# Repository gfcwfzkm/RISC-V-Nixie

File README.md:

# RISC-V-Nixie
Nixie Clock using the GD32VF103 RISC-V microcontroller by GigaDevices and the swiss precise RTC RV-3032-C7 by Micro Crystal AG.

For tubes, IN-8 tubes will be used as they can be mounted into sockets. Since the original, soviet sockets are quite bulky, individual pin sockets will be mounted instead.

## Status
The current status of the project, which steps are done or still need to be do. Currently only revision A is in testing, a revision that has some slight imperfections that will be tackled in the next revision. Since parts have been already delivered, revision A will be used to extensively test the PCB, in particular the dimming of the tubes and the high-voltage step-up circuitery.
Task | Comments
------------ | -------------
Initial Schematic | :heavy_check_mark:
Initial Layout & BOM | :heavy_check_mark:
Assembling PCB | :heavy_check_mark:
Power-ON Test, Voltage levels | :heavy_check_mark:
Initialising / Testing the MCU | :heavy_check_mark:
Writing basic I/O functions | In Progress... :grey_question:
Writing the clock programm | -

## Images

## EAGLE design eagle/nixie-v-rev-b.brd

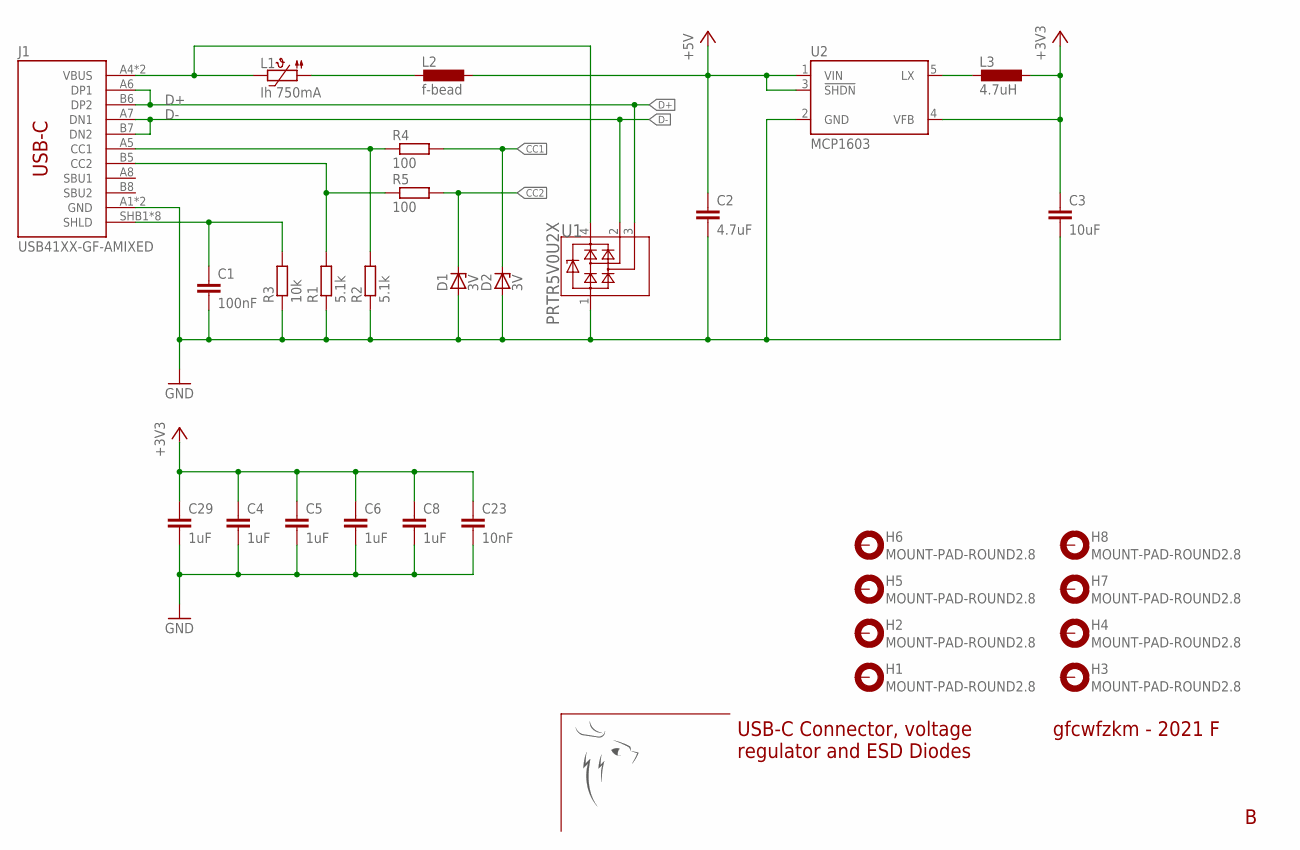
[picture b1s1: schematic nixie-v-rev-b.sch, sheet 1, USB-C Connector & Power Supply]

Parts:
C1: 100nF; C0603
C2: 4.7uF; C0805
C3: 10uF; C0805
C4, C5, C6, C8, C29: 1uF; C0603
C23: 10nF; C0603
D1, D2: 3V; SOD-523
H1, H2, H3, H4, H5, H6, H7, H8: MOUNT-PAD-ROUND2.8; 2,8-PAD
J1: USB41XX-GF-AMIXED; USB4105-GF-A
L1: Ih 750mA; R0805
L2: f-bead; R0805
L3: 4.7uH; R1210
R1, R2: 5.1k; R0603
R3: 10k; R0603
R4, R5: 100; R0603
U1: PRTR5V0U2X; SOT143B
U2: MCP1603; TSOT23-5
U$1: LOGO_PASCAL_GESELL30MM; LOGO_30MM

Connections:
+3V3: C3.1, C4.1, C5.1, C6.1, C8.1, C23.1, C29.1, L3.1, U2.4 (VFB); also elsewhere on the board
+5V: C2.1, L2.1, U2.1 (VIN), U2.3 (!SHDN); also elsewhere on the board
CC1: D2.C, R4.2; also elsewhere on the board
CC2: D1.C, R5.2; also elsewhere on the board
D+: J1.A6 (DP1), J1.B6 (DP2), U1.3; also elsewhere on the board
D-: J1.A7 (DN1), J1.B7 (DN2), U1.2; also elsewhere on the board
GND: C1.2, C2.2, C3.2, C4.2, C5.2, C6.2, C8.2, C23.2, C29.2, D1.A, D2.A, J1.A1 (GND), J1.B1 (GND), R1.1, R2.1, R3.1, U1.1, U2.2 (GND); also elsewhere on the board
LX: L3.2, U2.5 (LX)
unnamed: C1.1, J1.SHB1 (SHLD), J1.SHB2 (SHLD), J1.SHB3 (SHLD), J1.SHB4 (SHLD), J1.SHT1 (SHLD), J1.SHT2 (SHLD), J1.SHT3 (SHLD), J1.SHT4 (SHLD), R3.2
unnamed: J1.B5 (CC2), R1.2, R5.1
unnamed: J1.A5 (CC1), R2.2, R4.1
unnamed: L1.1, L2.2
VBUS: J1.A4 (VBUS), J1.B4 (VBUS), L1.2, U1.4

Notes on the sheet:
gfcwfzkm - 2021 F
USB-C Connector, voltage regulator and ESD Diodes

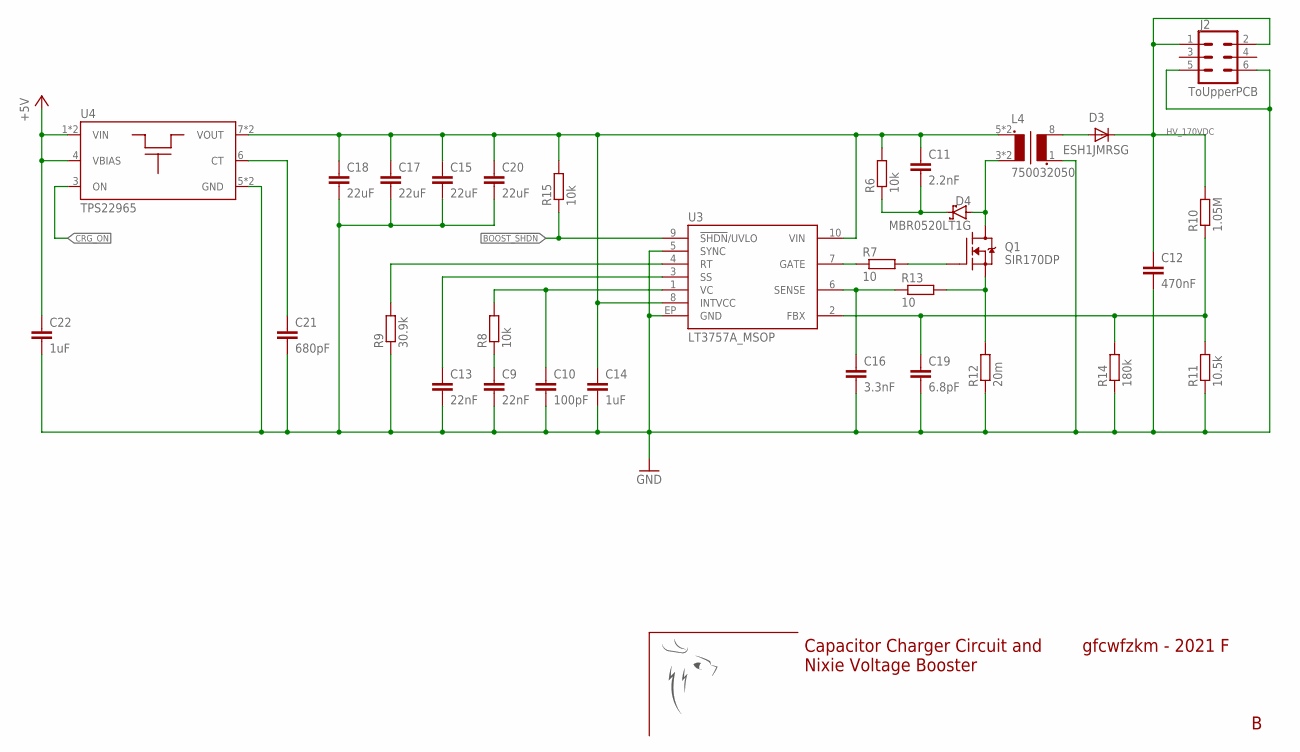
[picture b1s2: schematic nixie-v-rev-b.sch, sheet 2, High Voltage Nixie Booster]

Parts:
C9, C13: 22nF; C0603
C10: 100pF; C0603
C11: 2.2nF; C0603
C12: 470nF; C1812
C14, C22: 1uF; C0603
C15, C17, C18, C20: 22uF; C0805
C16: 3.3nF; C0603
C19: 6.8pF; C0603
C21: 680pF; C0603
D3: ESH1JMRSG; MICROSMA
D4: MBR0520LT1G; SOD-123
J2: ToUpperPCB; 2X3
L4: 750032050
Q1: SIR170DP; SO-08_POWERPAK
R6, R8, R15: 10k; R0603
R7, R13: 10; R0603
R9: 30.9k; R0603
R10: 1.05M; R0603
R11: 10.5k; R0603
R12: 20m; R0805
R14: 180k; R0603
U3: LT3757A_MSOP; MSOP10_POWER
U4: TPS22965; WSON-8
U$2: LOGO_PASCAL_GESELLEMPTY; EMPTY

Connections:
+5V: C22.1, U4.1 (VIN), U4.2 (VIN), U4.4 (VBIAS); also elsewhere on the board
BOOST_!SHDN: R15.1, U3.9 (!SHDN!/UVLO); also elsewhere on the board
CRG_ON: U4.3 (ON); also elsewhere on the board
FBX: C19.1, R10.1, R11.2, R14.2, U3.2 (FBX)
GATE: R7.1, U3.7 (GATE)
GND: C9.2, C10.2, C12.2, C13.2, C14.2, C15.2, C16.2, C17.2, C18.2, C19.2, C20.2, C21.2, C22.2, J2.5, J2.6, L4.1 (S1), R9.1, R11.1, R12.1, R14.1, U3.5 (SYNC), U3.EP (GND), U4.5 (GND), U4.TP (GND); also elsewhere on the board
HV_170VDC: C12.1, D3.C, J2.1, J2.2, R10.2
unnamed: C11.2, D4.C, R6.1
unnamed: Q1.4 (G), R7.2
unnamed: D3.A, L4.8 (S2)
unnamed: C9.1, R8.1
unnamed: Q1.1 (S), Q1.2 (S), Q1.3 (S), R12.2, R13.2
unnamed: D4.A, L4.3 (P2), L4.4 (P2), Q1.5 (D), Q1.6 (D), Q1.7 (D), Q1.8 (D), Q1.THERMAL (D)
unnamed: C21.1, U4.6 (CT)
RT: R9.2, U3.4 (RT)
SENSE: C16.1, R13.1, U3.6 (SENSE)
SS: C13.1, U3.3 (SS)
SUP_BOOST: C11.1, C14.1, C15.1, C17.1, C18.1, C20.1, L4.5 (P1), L4.6 (P1), R6.2, R15.2, U3.8 (INTVCC), U3.10 (VIN), U4.7 (VOUT), U4.8 (VOUT)
VC: C10.1, R8.2, U3.1 (VC)

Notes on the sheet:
Capacitor Charger Circuit and Nixie Voltage Booster
gfcwfzkm - 2021 F

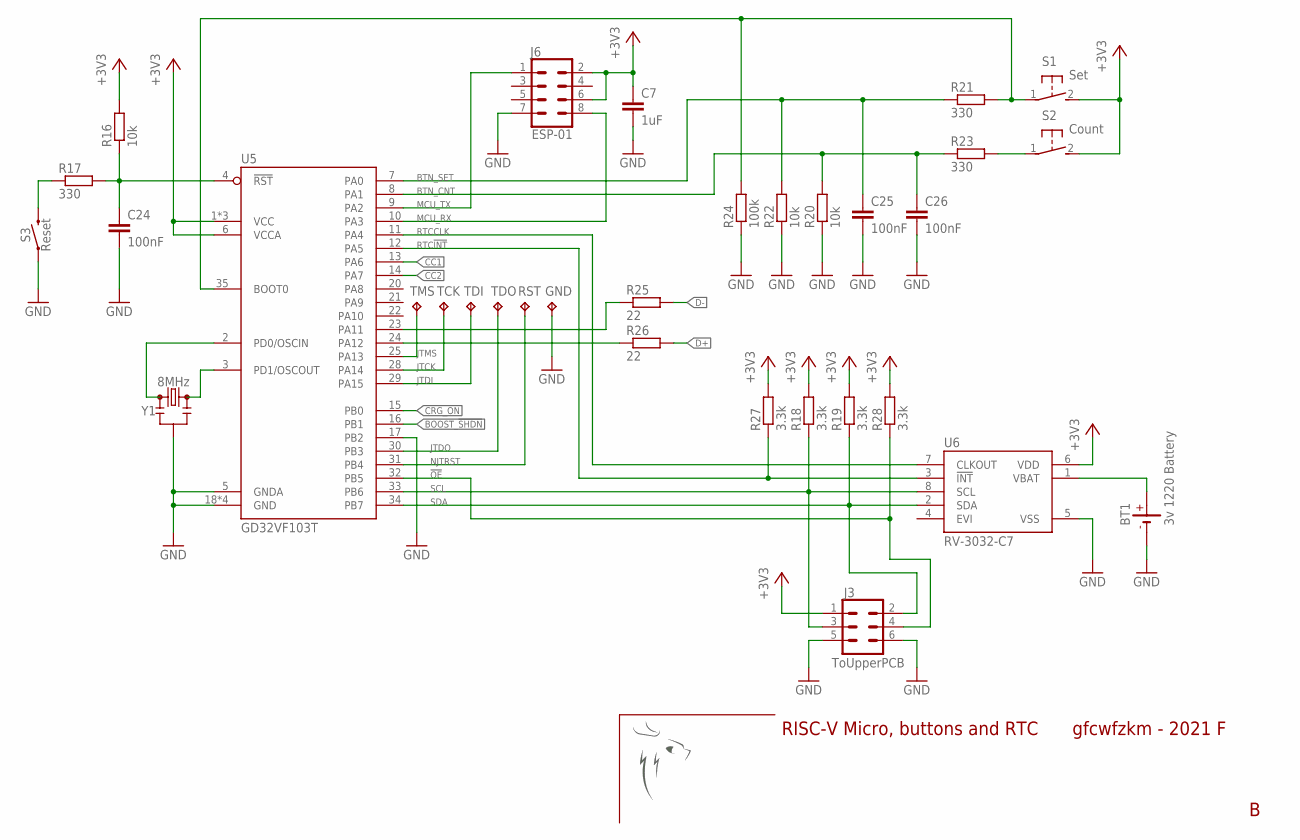
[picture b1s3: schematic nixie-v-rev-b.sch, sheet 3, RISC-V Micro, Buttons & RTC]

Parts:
BT1: 3v 1220 Battery; CH291-1220LF
C7: 1uF; C0603
C24, C25, C26: 100nF; C0603
GND: TPB1,27; B1,27
J3: ToUpperPCB; 2X3
J6: ESP-01; 2X4
R16, R20, R22: 10k; R0603
R17, R21, R23: 330; R0603
R18, R19, R27, R28: 3.3k; R0603
R24: 100k; R0603
R25, R26: 22; R0603
RST: TPB1,27; B1,27
S1: Set; B3F-31XX
S2: Count; B3F-31XX
S3: Reset; TACTILE_SWITCH_SMD_6.0X3.5MM
TCK: TPB1,27; B1,27
TDI: TPB1,27; B1,27
TDO: TPB1,27; B1,27
TMS: TPB1,27; B1,27
U5: GD32VF103T; QFN-36
U6: RV-3032-C7; RV-3028-C7
U$3: LOGO_PASCAL_GESELLEMPTY; EMPTY
Y1: 8MHz; RESONATOR-SMD-3.2X1.3

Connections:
!OE: J3.4, R28.1, U5.32 (PB5)
+3V3: C7.1, J3.1, J6.2, J6.6, R16.2, R18.2, R19.2, R27.2, R28.2, S1.2 (S), S2.2 (S), U5.1 (VCC), U5.6 (VCCA), U5.19 (VCC), U5.27 (VCC), U6.6 (VDD); also elsewhere on the board
BOOST_!SHDN: U5.16 (PB1); also elsewhere on the board
BTN_CNT: C26.1, R20.2, R23.1, U5.8 (PA1)
BTN_SET: C25.1, R21.1, R22.2, U5.7 (PA0)
CC1: U5.13 (PA6); also elsewhere on the board
CC2: U5.14 (PA7); also elsewhere on the board
CRG_ON: U5.15 (PB0); also elsewhere on the board
D+: R26.2; also elsewhere on the board
D-: R25.2; also elsewhere on the board
GND: BT1.-, C7.2, C24.2, C25.2, C26.2, GND.TP, J3.5, J3.6, J6.7, R20.1, R22.1, R24.1, S3.1, U5.5 (GNDA), U5.17 (PB2), U5.18 (GND), U5.26 (GND), U5.36 (GND), U5.EP (GND), U6.5 (VSS), Y1.2; also elsewhere on the board
JTCK: TCK.TP, U5.28 (PA14)
JTDI: TDI.TP, U5.29 (PA15)
JTDO: TDO.TP, U5.30 (PB3)
JTMS: TMS.TP, U5.25 (PA13)
MCU_RX: J6.8, U5.10 (PA3)
MCU_TX: J6.1, U5.9 (PA2)
unnamed: C24.1, R16.1, R17.2, U5.4 (!RST)
unnamed: R26.1, U5.24 (PA12)
unnamed: R23.2, S2.1
unnamed: U5.3 (PD1/OSCOUT), Y1.3
unnamed: R21.2, R24.2, S1.1, U5.35 (BOOT0)
unnamed: R17.1, S3.2
unnamed: U5.2 (PD0/OSCIN), Y1.1
unnamed: R25.1, U5.23 (PA11)
unnamed: BT1.+, U6.1 (VBAT)
NJTRST: RST.TP, U5.31 (PB4)
RTC!INT: R27.1, U5.12 (PA5), U6.3 (!INT)
RTCCLK: U5.11 (PA4), U6.7 (CLKOUT)
SCL: J3.3, R18.1, U5.33 (PB6), U6.8 (SCL)
SDA: J3.2, R19.1, U5.34 (PB7), U6.2 (SDA)

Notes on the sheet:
RISC-V Micro, buttons and RTC
gfcwfzkm - 2021 F

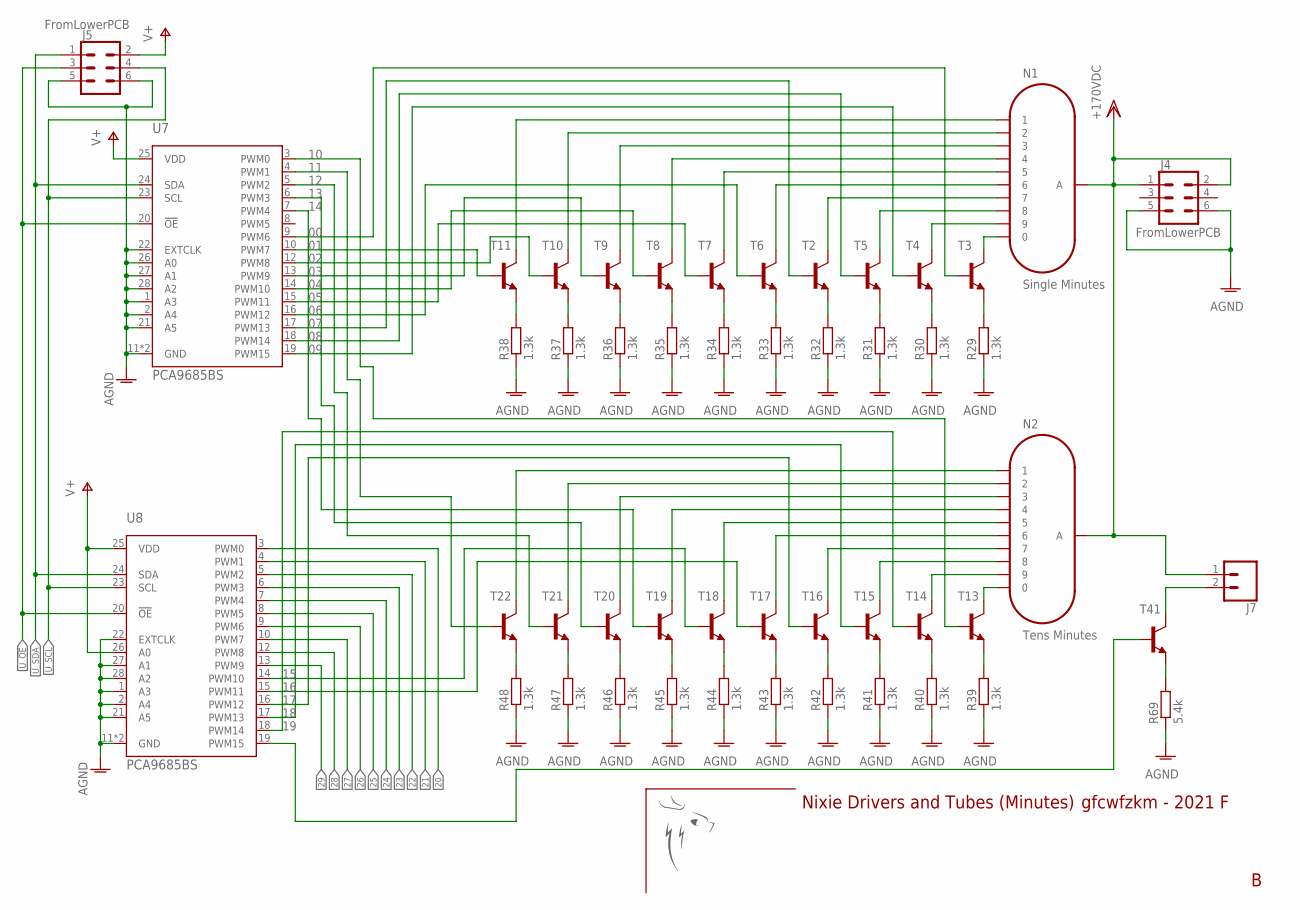
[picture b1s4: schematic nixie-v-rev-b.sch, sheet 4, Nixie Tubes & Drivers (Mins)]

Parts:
J4, J5: FromLowerPCB; 2X3
J7: CONN_02; 1X02
N1: Single Minutes; IN-8
N2: Tens Minutes; IN-8
R29, R30, R31, R32, R33, R34, R35, R36, R37, R38, R39, R40, R41, R42, R43, R44, R45, R46, R47, R48: 1.3k; R0603
R69: 5.4k; R0603
T2, T3, T4, T5, T6, T7, T8, T9, T10, T11, T13, T14, T15, T16, T17, T18, T19, T20, T21, T22, T41: MSD42WT1G; SC70-3-R
U7, U8: PCA9685BS; HVQFN28
U$4: LOGO_PASCAL_GESELLEMPTY; EMPTY

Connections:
00: T3.1 (B), U7.9 (PWM6)
01: T11.1 (B), U7.10 (PWM7)
02: T10.1 (B), U7.12 (PWM8)
03: T9.1 (B), U7.13 (PWM9)
04: T8.1 (B), U7.14 (PWM10)
05: T7.1 (B), U7.15 (PWM11)
06: T6.1 (B), U7.16 (PWM12)
07: T2.1 (B), U7.17 (PWM13)
08: T5.1 (B), U7.18 (PWM14)
09: T4.1 (B), U7.19 (PWM15)
10: T13.1 (B), U7.3 (PWM0)
11: T22.1 (B), U7.4 (PWM1)
12: T21.1 (B), U7.5 (PWM2)
13: T20.1 (B), U7.6 (PWM3)
14: T19.1 (B), U7.7 (PWM4)
15: T18.1 (B), U8.14 (PWM10)
16: T17.1 (B), U8.15 (PWM11)
17: T16.1 (B), U8.16 (PWM12)
18: T15.1 (B), U8.17 (PWM13)
19: T14.1 (B), U8.18 (PWM14)
20: U8.3 (PWM0); also elsewhere on the board
21: U8.4 (PWM1); also elsewhere on the board
22: U8.5 (PWM2); also elsewhere on the board
23: U8.6 (PWM3); also elsewhere on the board
24: U8.7 (PWM4); also elsewhere on the board
25: U8.8 (PWM5); also elsewhere on the board
26: U8.9 (PWM6); also elsewhere on the board
27: U8.10 (PWM7); also elsewhere on the board
28: U8.12 (PWM8); also elsewhere on the board
29: U8.13 (PWM9); also elsewhere on the board
+170VDC: J4.1, J4.2, J7.1, N1.A, N2.A; also elsewhere on the board
AGND: J4.5, J4.6, J5.5, J5.6, R29.1, R30.1, R31.1, R32.1, R33.1, R34.1, R35.1, R36.1, R37.1, R38.1, R39.1, R40.1, R41.1, R42.1, R43.1, R44.1, R45.1, R46.1, R47.1, R48.1, R69.1, U7.1 (A3), U7.2 (A4), U7.11 (GND), U7.21 (A5), U7.22 (EXTCLK), U7.26 (A0), U7.27 (A1), U7.28 (A2), U7.TH (GND), U8.1 (A3), U8.2 (A4), U8.11 (GND), U8.21 (A5), U8.22 (EXTCLK), U8.27 (A1), U8.28 (A2), U8.TH (GND); also elsewhere on the board
unnamed: N1.0, T3.3 (C)
unnamed: J7.2, T41.3 (C)
unnamed: R69.2, T41.2 (E)
unnamed: T41.1 (B), U8.19 (PWM15)
unnamed: N1.9, T4.3 (C)
unnamed: N1.8, T5.3 (C)
unnamed: N1.7, T2.3 (C)
unnamed: N1.6, T6.3 (C)
unnamed: N1.5, T7.3 (C)
unnamed: N1.4, T8.3 (C)
unnamed: N1.3, T9.3 (C)
unnamed: N1.2, T10.3 (C)
unnamed: N1.1, T11.3 (C)
unnamed: R29.2, T3.2 (E)
unnamed: R38.2, T11.2 (E)
unnamed: R37.2, T10.2 (E)
unnamed: R36.2, T9.2 (E)
unnamed: R35.2, T8.2 (E)
unnamed: R34.2, T7.2 (E)
unnamed: R33.2, T6.2 (E)
unnamed: R32.2, T2.2 (E)
unnamed: R31.2, T5.2 (E)
unnamed: R30.2, T4.2 (E)
unnamed: N2.0, T13.3 (C)
unnamed: N2.9, T14.3 (C)
unnamed: N2.8, T15.3 (C)
unnamed: N2.7, T16.3 (C)
unnamed: N2.6, T17.3 (C)
unnamed: N2.5, T18.3 (C)
unnamed: N2.4, T19.3 (C)
unnamed: N2.3, T20.3 (C)
unnamed: N2.2, T21.3 (C)
unnamed: N2.1, T22.3 (C)
unnamed: R39.2, T13.2 (E)
unnamed: R48.2, T22.2 (E)
unnamed: R47.2, T21.2 (E)
unnamed: R46.2, T20.2 (E)
unnamed: R45.2, T19.2 (E)
unnamed: R44.2, T18.2 (E)
unnamed: R43.2, T17.2 (E)
unnamed: R42.2, T16.2 (E)
unnamed: R41.2, T15.2 (E)
unnamed: R40.2, T14.2 (E)
U_!OE: J5.3, U7.20 (!OE), U8.20 (!OE); also elsewhere on the board
U_SCL: J5.4, U7.23 (SCL), U8.23 (SCL); also elsewhere on the board
U_SDA: J5.1, U7.24 (SDA), U8.24 (SDA); also elsewhere on the board
V+: J5.2, U7.25 (VDD), U8.25 (VDD), U8.26 (A0); also elsewhere on the board

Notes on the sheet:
Nixie Drivers and Tubes (Minutes)
gfcwfzkm - 2021 F

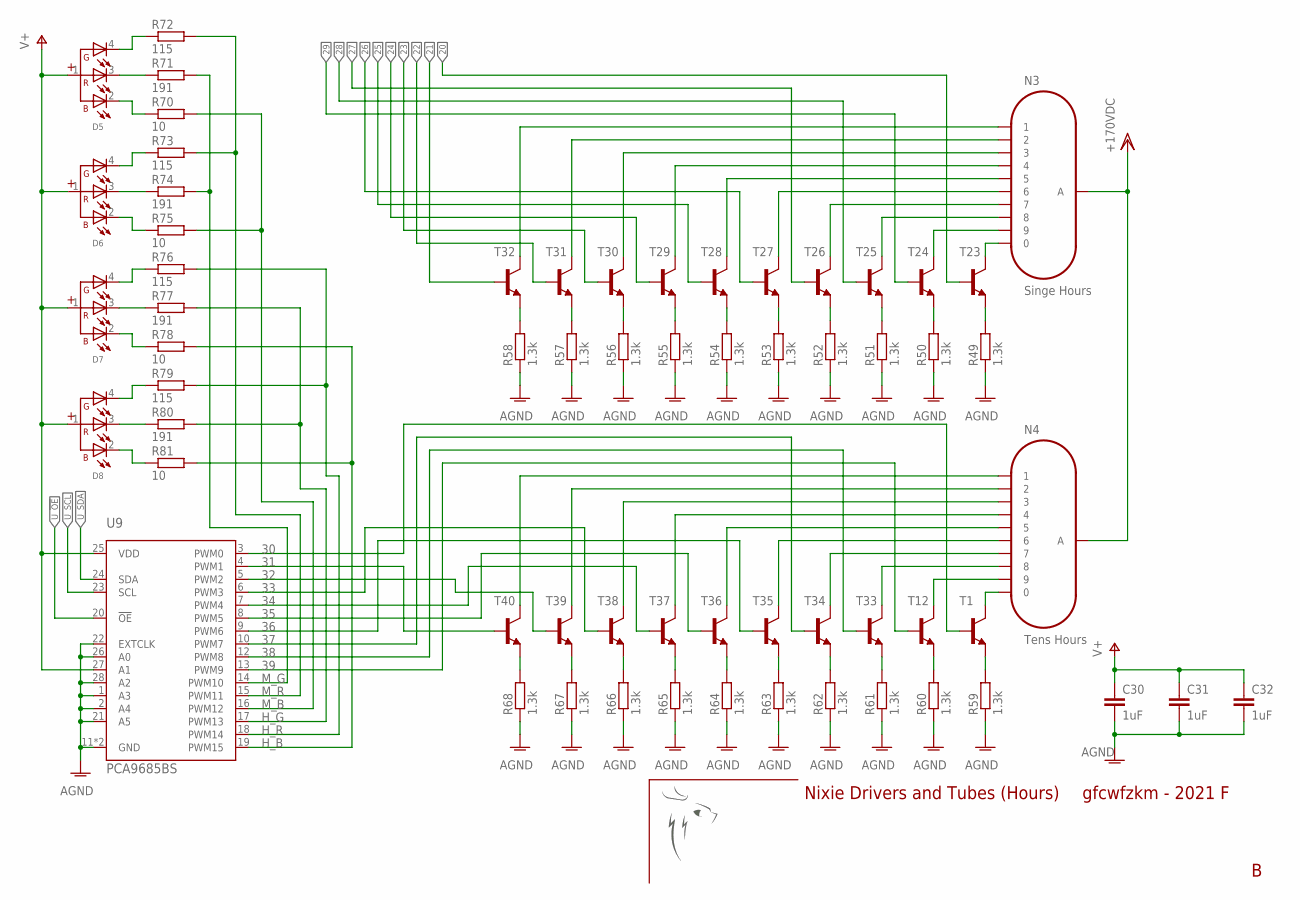
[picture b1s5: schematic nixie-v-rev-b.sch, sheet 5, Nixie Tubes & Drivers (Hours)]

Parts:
C30, C31, C32: 1uF; C0603
D5, D6, D7, D8: WL-SFRW_1206_REC_156120M173000_NOR; WL-SFRW_1206_REC
N3: Singe Hours; IN-8
N4: Tens Hours; IN-8
R49, R50, R51, R52, R53, R54, R55, R56, R57, R58, R59, R60, R61, R62, R63, R64, R65, R66, R67, R68: 1.3k; R0603
R70, R75, R78, R81: 10; R0603
R71, R74, R77, R80: 191; R0603
R72, R73, R76, R79: 115; R0603
T1, T12, T23, T24, T25, T26, T27, T28, T29, T30, T31, T32, T33, T34, T35, T36, T37, T38, T39, T40: MSD42WT1G; SC70-3-R
U9: PCA9685BS; HVQFN28
U$5: LOGO_PASCAL_GESELLEMPTY; EMPTY

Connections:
20: T23.1 (B); also elsewhere on the board
21: T32.1 (B); also elsewhere on the board
22: T31.1 (B); also elsewhere on the board
23: T30.1 (B); also elsewhere on the board
24: T29.1 (B); also elsewhere on the board
25: T28.1 (B); also elsewhere on the board
26: T27.1 (B); also elsewhere on the board
27: T26.1 (B); also elsewhere on the board
28: T25.1 (B); also elsewhere on the board
29: T24.1 (B); also elsewhere on the board
30: T1.1 (B), U9.3 (PWM0)
31: T40.1 (B), U9.4 (PWM1)
32: T39.1 (B), U9.5 (PWM2)
33: T38.1 (B), U9.6 (PWM3)
34: T37.1 (B), U9.7 (PWM4)
35: T36.1 (B), U9.8 (PWM5)
36: T35.1 (B), U9.9 (PWM6)
37: T34.1 (B), U9.10 (PWM7)
38: T33.1 (B), U9.12 (PWM8)
39: T12.1 (B), U9.13 (PWM9)
+170VDC: N3.A, N4.A; also elsewhere on the board
AGND: C30.2, C31.2, C32.2, R49.1, R50.1, R51.1, R52.1, R53.1, R54.1, R55.1, R56.1, R57.1, R58.1, R59.1, R60.1, R61.1, R62.1, R63.1, R64.1, R65.1, R66.1, R67.1, R68.1, U9.1 (A3), U9.2 (A4), U9.11 (GND), U9.21 (A5), U9.22 (EXTCLK), U9.26 (A0), U9.28 (A2), U9.TH (GND); also elsewhere on the board
H_B: R78.2, R81.2, U9.19 (PWM15)
H_G: R77.2, R80.2, U9.17 (PWM13)
H_R: R76.2, R79.2, U9.18 (PWM14)
M_B: R70.2, R75.2, U9.16 (PWM12)
M_G: R71.2, R74.2, U9.14 (PWM10)
M_R: R72.2, R73.2, U9.15 (PWM11)
unnamed: N3.0, T23.3 (C)
unnamed: N3.9, T24.3 (C)
unnamed: N3.8, T25.3 (C)
unnamed: N3.7, T26.3 (C)
unnamed: N3.6, T27.3 (C)
unnamed: N3.5, T28.3 (C)
unnamed: N3.4, T29.3 (C)
unnamed: N3.3, T30.3 (C)
unnamed: N3.2, T31.3 (C)
unnamed: N3.1, T32.3 (C)
unnamed: R49.2, T23.2 (E)
unnamed: R58.2, T32.2 (E)
unnamed: R57.2, T31.2 (E)
unnamed: R56.2, T30.2 (E)
unnamed: R55.2, T29.2 (E)
unnamed: R54.2, T28.2 (E)
unnamed: R53.2, T27.2 (E)
unnamed: R52.2, T26.2 (E)
unnamed: R51.2, T25.2 (E)
unnamed: R50.2, T24.2 (E)
unnamed: N4.0, T1.3 (C)
unnamed: N4.9, T12.3 (C)
unnamed: N4.8, T33.3 (C)
unnamed: N4.7, T34.3 (C)
unnamed: N4.6, T35.3 (C)
unnamed: N4.5, T36.3 (C)
unnamed: N4.4, T37.3 (C)
unnamed: N4.3, T38.3 (C)
unnamed: N4.2, T39.3 (C)
unnamed: N4.1, T40.3 (C)
unnamed: R59.2, T1.2 (E)
unnamed: R68.2, T40.2 (E)
unnamed: R67.2, T39.2 (E)
unnamed: R66.2, T38.2 (E)
unnamed: R65.2, T37.2 (E)
unnamed: R64.2, T36.2 (E)
unnamed: R63.2, T35.2 (E)
unnamed: R62.2, T34.2 (E)
unnamed: R61.2, T33.2 (E)
unnamed: R60.2, T12.2 (E)
unnamed: D5.4 (G-), R72.1
unnamed: D5.3 (R-), R71.1
unnamed: D5.2 (B-), R70.1
unnamed: D8.4 (G-), R79.1
unnamed: D8.3 (R-), R80.1
unnamed: D8.2 (B-), R81.1
unnamed: D6.4 (G-), R73.1
unnamed: D6.3 (R-), R74.1
unnamed: D6.2 (B-), R75.1
unnamed: D7.2 (B-), R78.1
unnamed: D7.3 (R-), R77.1
unnamed: D7.4 (G-), R76.1
U_!OE: U9.20 (!OE); also elsewhere on the board
U_SCL: U9.23 (SCL); also elsewhere on the board
U_SDA: U9.24 (SDA); also elsewhere on the board
V+: C30.1, C31.1, C32.1, D5.1 (+), D6.1 (+), D7.1 (+), D8.1 (+), U9.25 (VDD), U9.27 (A1); also elsewhere on the board

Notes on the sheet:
Nixie Drivers and Tubes (Hours)
gfcwfzkm - 2021 F

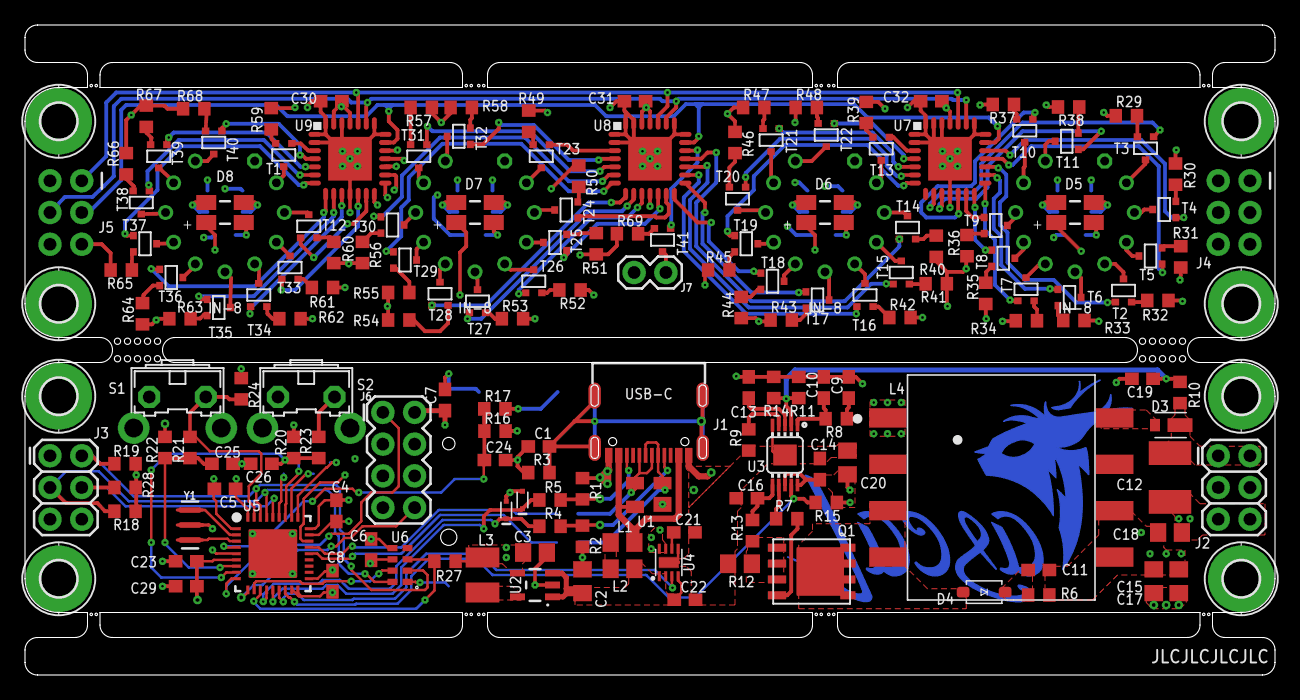
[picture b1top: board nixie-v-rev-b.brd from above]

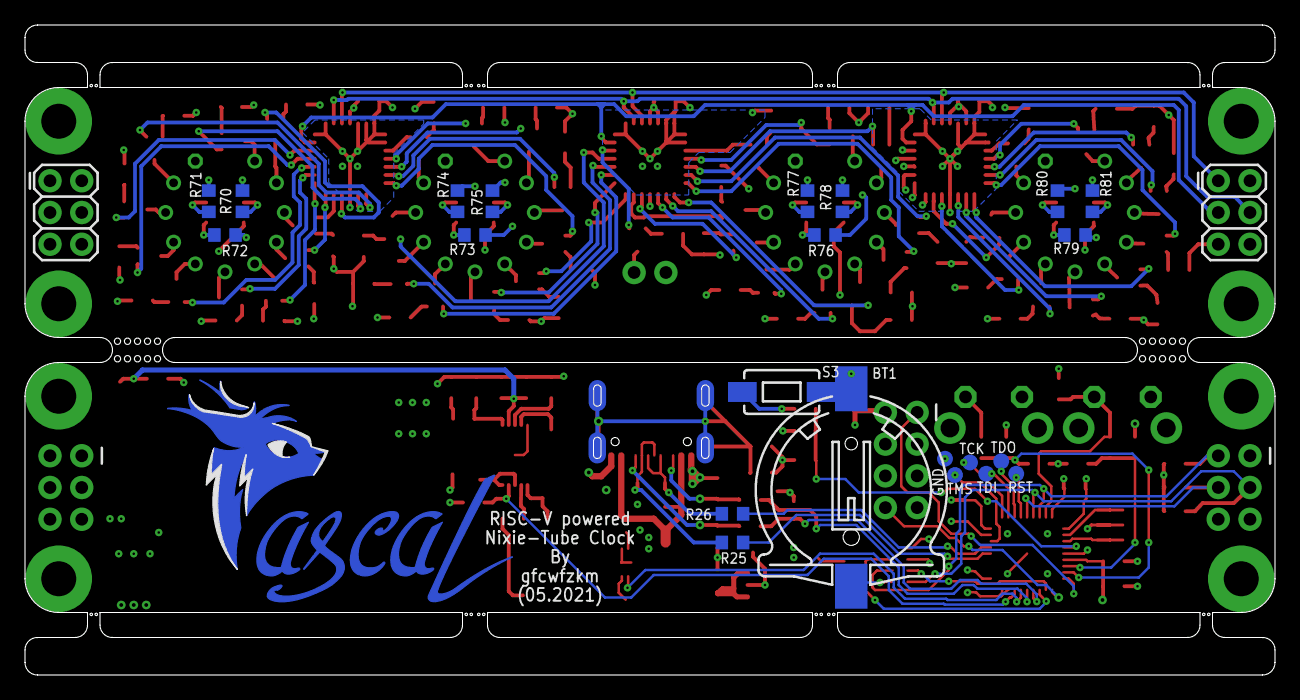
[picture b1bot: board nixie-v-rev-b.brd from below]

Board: 4 copper layers, 100.0 x 52.0 mm, 209 parts (25 on the bottom side), 200 nets.

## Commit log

2021-05-06 Create temp
2021-05-06 Initial upload of the schematics & layout
2021-05-06 Initial upload
    Contains Gerber ZIP, PDF Exports of the eagle schematics & layout as well as the BOM as excel
2021-06-15 Uploaded images of initial Revision A prototype
    Images of the first revision prototype, including a basic power-ON test with the LEDs turned on.
2021-06-15 Updated with Status and Images
2021-06-15 Added Info of the circuit / project
2021-10-18 linked firmware to hardware project
2021-10-18 removed old code folder

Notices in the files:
parts and their libraries:
SparkFun-Switches: Licensing: Creative Commons ShareAlike 4.0 International - https://creativecommons.org/licenses/by-sa/4.0
Wurth_LEDs_WL-SFRW: Copyright: Würth Elektronik
